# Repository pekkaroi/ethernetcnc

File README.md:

# ethernetcnc

This is my project for controlling CNC machine via ethernet port using LinuxCNC. It was originally shortly instroduced at http://pekka.eu/cnc. After receiving questions about it every now and then, I decided to publish it.

There is very little to no documentation about the project right now - hopefully that will change some day. There is the firmware for STM32F407, the kicad PCB and a LinuxCNC driver available.

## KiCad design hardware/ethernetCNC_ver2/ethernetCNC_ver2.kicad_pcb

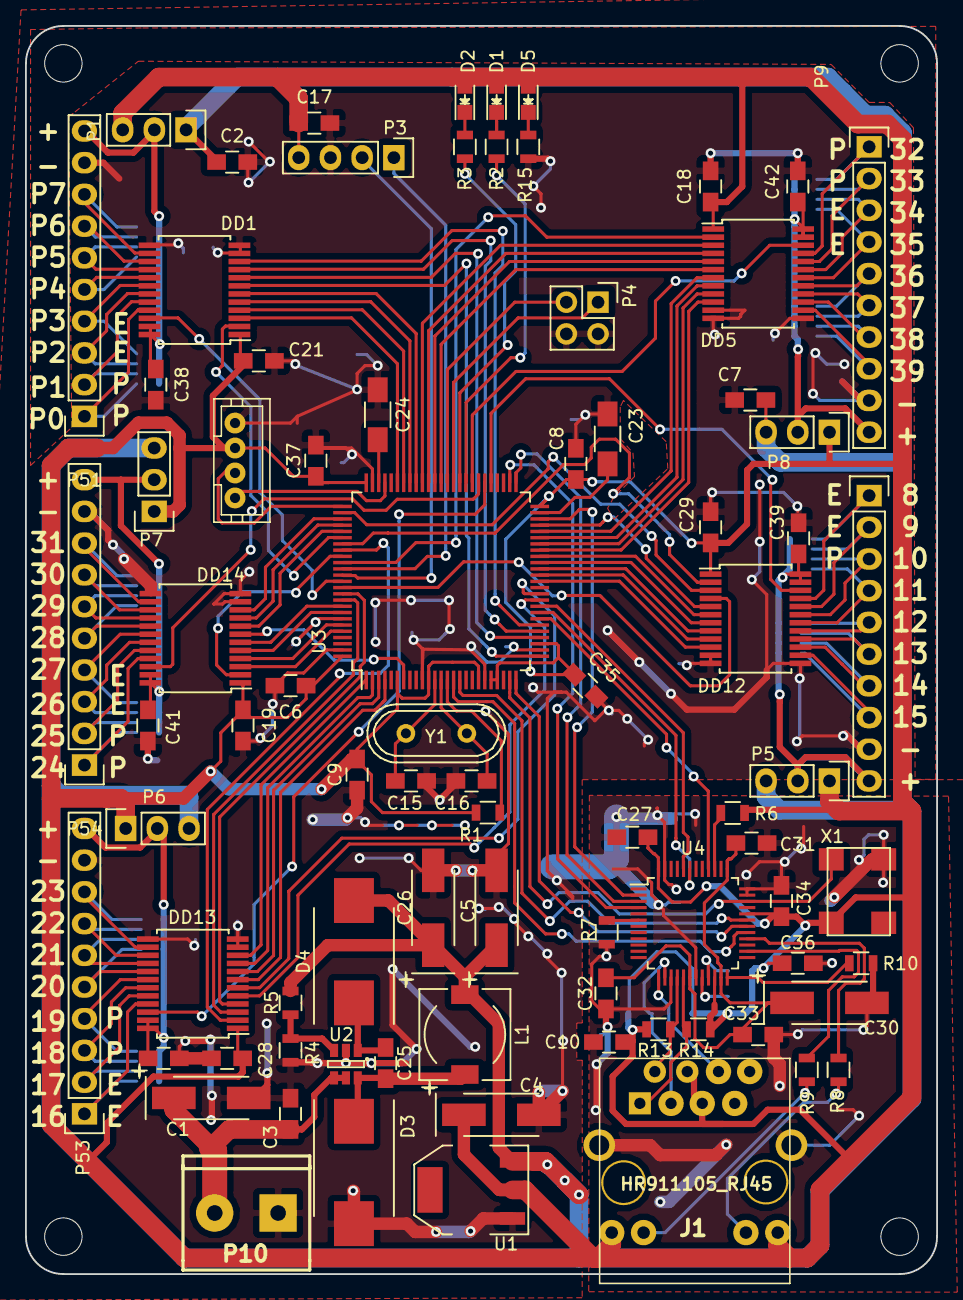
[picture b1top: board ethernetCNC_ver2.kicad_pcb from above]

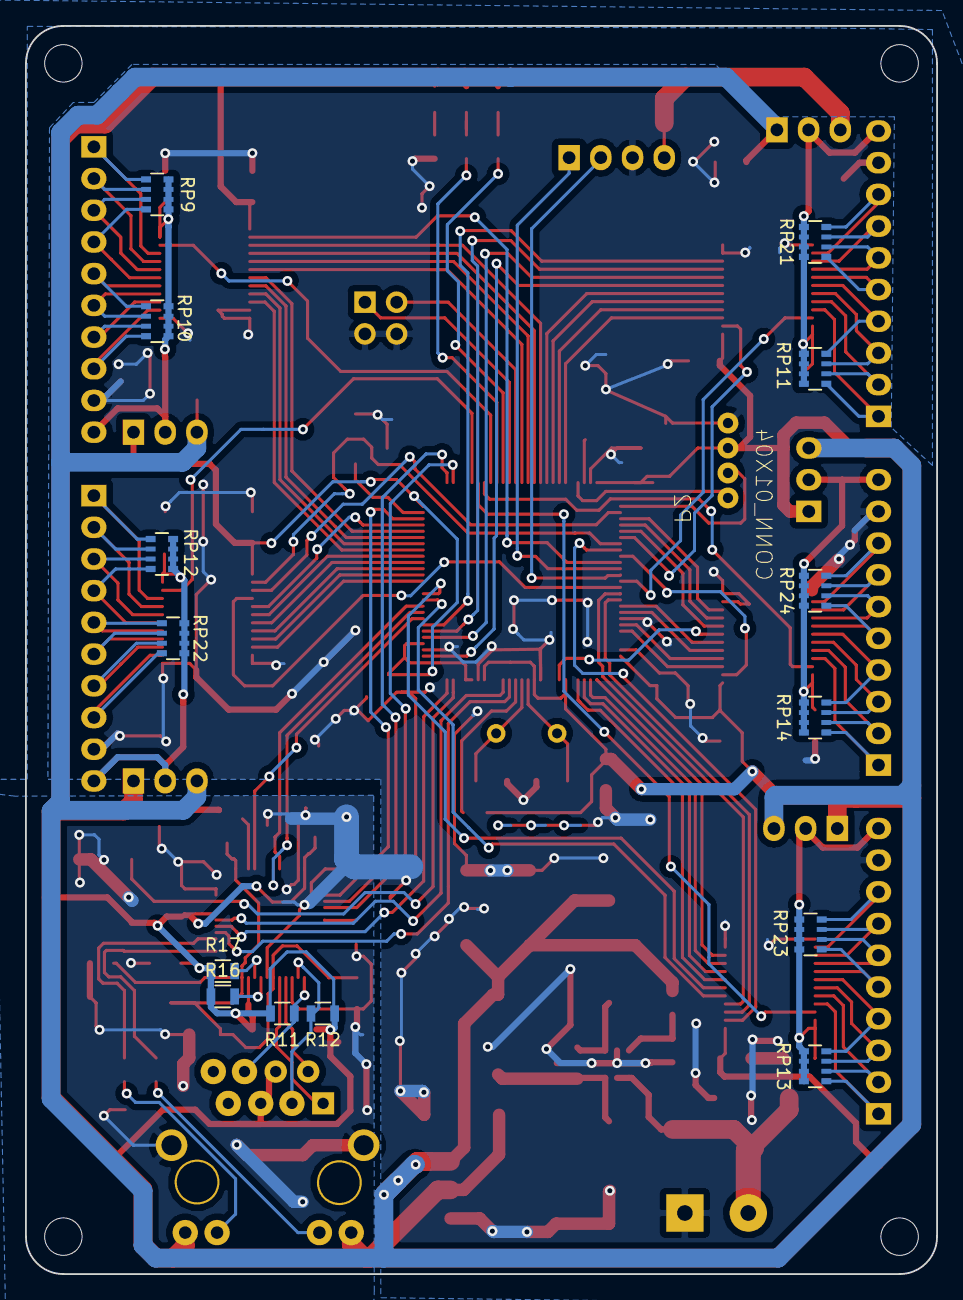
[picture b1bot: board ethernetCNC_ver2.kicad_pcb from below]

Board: 2 copper layers, 73.0 x 100.0 mm, 99 parts (14 on the bottom side), 142 nets.

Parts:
C1, C26: CP; TantalC_SizeC_EIA-6032_HandSoldering
C2, C3, C6, C7, C8, C9, C10, C17, C18, C19, C21, C25, C27, C28, C29, C31, C32, C33, C34, C35, C36, C37, C38, C39, C40, C41, C42: 100n; C_0805_HandSoldering
C4, C5, C30: 10u; TantalC_SizeC_EIA-6032_HandSoldering
C15, C16: 22p; C_0805_HandSoldering
C23, C24: 2.2u; C_1206_HandSoldering
D1, D2, D5: Led_Small; LED-0805
D3: D_Schottky_Small; DO-214AB_Handsoldering
D4: D; DO-214AB_Handsoldering
DD1, DD5, DD12, DD13, DD14: SN74LVC8T245; SSOP-24_5.3x8.2mm_Pitch0.65mm
J1: HR911105_RJ45
L1: L_Small; Choke_SMD_7.3x7.3_H3.5
P1, P5, P6, P7, P8: CONN_01X03; Pin_Header_Straight_1x03
P2: CONN_01X04; jst-ph-JST-PH4
P3: CONN_01X04; Pin_Header_Straight_1x04
P4: CONN_02X02; Pin_Header_Straight_2x02
P9, P51, P52, P53, P54: CONN_01X10; Pin_Header_Straight_1x10
P10: CONN_01X02; mors_2p
P11, P12, P13, P14: CONN_01X01; MountingHole_3mm
R1, R2, R3, R4, R5, R8, R9, R15, R16, R17: R; R_0805
R6, R7: 2k2; R_0805
R10: 4.87k 1%; R_0805
R11, R12, R13, R14: 50; R_0805
RP9, RP10, RP11, RP12, RP13, RP14, RP21, RP22, RP23, RP24: R_PACK4; R_Array_Convex_4x0603
U1: NCP1117ST50T3G; SOT-223
U2: LM2734; SOT-23-6
U3: STM32F407VG; LQFP-100_14x14mm_Pitch0.5mm
U4: DP83848; LQFP-48_7x7mm_Pitch0.5mm
X1: OSCILLATOR-VDD-4; OSC_4P_7050
Y1: Crystal_Small; Crystal_HC49-U_Vertical

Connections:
+3V3: C4.1, C6.1, C8.1, C9.1, C10.1, C17.1, C18.1, C19.1, C21.1, C27.1, C28.1, C29.1, C34.1, C35.1, C36.1, C37.1, D1.2, D2.2, D5.2, DD1.1, DD5.1, DD12.1, DD13.1, DD14.1, J1.4, J1.5, J1.9, J1.12, P1.3, P2.3, P3.4, P5.1, P6.1, P7.1, P8.1, R1.1, R6.2, R11.2, R12.1, R13.2, R14.1, R16.1, R17.1, U1.2, U3.6, U3.11, U3.19, U3.21, U3.22, U3.28, U3.50, U3.75, U3.100, U4.22, U4.32, U4.48, X1.4
+5V: C2.1, C5.1, C7.1, C26.1, D4.2, L1.2, P1.1, P5.3, P6.3, P7.3, P8.3, R5.1, U1.3
/Bank1/I1: DD1.3, U3.70
/Bank1/I2: DD1.4, U3.69
/Bank1/I5: DD1.7, U3.26
/Bank1/I6: DD1.8, U3.29
/Bank1/I7: DD1.9, U3.30
/Bank1/I8: DD1.10, U3.31
/Bank2/I3: DD12.5, U3.47
/Bank2/I4: DD12.6, U3.42
/Bank2/I5: DD12.7, U3.41
/Bank2/I6: DD12.8, U3.40
/Bank2/I7: DD12.9, U3.39
/Bank2/I8: DD12.10, U3.38
/Bank3/I3: DD13.5, U3.35
/Bank3/I4: DD13.6, U3.36
/Bank3/I5: DD13.7, U3.4
/Bank3/I6: DD13.8, U3.3
/Bank3/I7: DD13.9, U3.2
/Bank3/I8: DD13.10, U3.1
/Bank4/I1: DD14.3, U3.96
/Bank4/I2: DD14.4, U3.95
/Bank4/I5: DD14.7, U3.7
/Bank4/I6: DD14.8, U3.80
/Bank4/I7: DD14.9, U3.79
/Bank4/I8: DD14.10, U3.78
/Bank5/I1: DD5.3, U3.66
/Bank5/I2: DD5.4, U3.65
/Bank5/I5: DD5.7, U3.46
/Bank5/I6: DD5.8, U3.45
/Bank5/I7: DD5.9, U3.44
/Bank5/I8: DD5.10, U3.43
/VIN: C1.1, C3.1, P10.2, U2.4, U2.5
/uC/BANK1_DIR: DD1.2, U3.81
/uC/BANK1_OE: DD1.22, U3.88
/uC/BANK2_DIR: DD12.2, U3.82
/uC/BANK2_OE: DD12.22, U3.55
/uC/BANK3_DIR: DD13.2, U3.83
/uC/BANK3_OE: DD13.22, U3.56
/uC/BANK4_DIR: DD14.2, U3.84
/uC/BANK4_OE: DD14.22, U3.57
/uC/BANK5_DIR: DD5.2, U3.85
/uC/BANK5_OE: DD5.22, U3.58
/uC/CRS: U3.32, U4.40
/uC/ELED0: J1.10, R9.1
/uC/ELED1: J1.11, R8.1
/uC/ENC1A: DD1.6, U3.67
/uC/ENC1B: DD1.5, U3.68
/uC/ENC2A: DD12.3, U3.77
/uC/ENC2B: DD12.4, U3.89
/uC/ENC3A: DD13.4, U3.90
/uC/ENC3B: DD13.3, U3.91
/uC/ENC4A: DD14.6, U3.92
/uC/ENC4B: DD14.5, U3.93
/uC/ENC8A: DD5.6, U3.63
/uC/ENC8B: DD5.5, U3.64
/uC/EOSC: U3.24, U4.34, X1.3
/uC/ERESET: U3.15, U4.29
/uC/LED0: R2.2, U3.59
/uC/LED1: R3.2, U3.60
/uC/MDC: U3.16, U4.31
/uC/MDIO: U3.25, U4.30
/uC/RX0: U3.33, U4.43
/uC/RX1: U3.34, U4.44
/uC/STATUS0: P4.1, U3.61
/uC/STATUS1: P4.3, U3.62
/uC/TX0: U3.51, U4.3
/uC/TX1: U3.52, U4.4
/uC/TX_EN: U3.48, U4.2
GND: C1.2, C2.2, C3.2, C4.2, C5.2, C6.2, C7.2, C8.2, C9.2, C10.2, C15.2, C16.2, C17.2, C18.2, C19.2, C21.2, C23.2, C24.2, C26.2, C27.2, C28.2, C29.2, C30.2, C31.2, C32.2, C33.2, C34.2, C35.2, C36.2, C37.2, C38.2, C39.2, C40.2, C41.2, C42.2, D3.2, DD1.11, DD1.12, DD1.13, DD5.11, DD5.12, DD5.13, DD12.11, DD12.12, DD12.13, DD13.11, DD13.12, DD13.13, DD14.11, DD14.12, DD14.13, J1.0, P2.4, P3.3, P4.2, P4.4, P9.9, P10.1, P51.9, P52.9, P53.9, P54.9, R4.1, R7.1, R10.1, R15.2, U1.1, U2.2, U3.10, U3.20, U3.27, U3.74, U3.94, U3.99, U4.15, U4.19, U4.35, U4.36, U4.47, X1.2
unnamed: C15.1, U3.12, Y1.1
unnamed: C16.1, U3.13, Y1.2
unnamed: C23.1, U3.49
unnamed: C24.1, U3.73
unnamed: C25.1, D4.1, U2.1
unnamed: C25.2, D3.1, L1.1, U2.6
unnamed: C30.1, C31.1, C32.1, C33.1, U4.18, U4.23, U4.37
unnamed: C38.1, DD1.23, DD1.24, P1.2, P51.10, RP11.1, RP11.2, RP11.3, RP11.4, RP21.1, RP21.2, RP21.3, RP21.4
unnamed: C39.1, DD12.23, DD12.24, P5.2, P52.10, RP12.1, RP12.2, RP12.3, RP12.4, RP22.1, RP22.2, RP22.3, RP22.4
unnamed: C40.1, DD13.23, DD13.24, P6.2, P53.10, RP13.1, RP13.2, RP13.3, RP13.4, RP23.1, RP23.2, RP23.3, RP23.4
unnamed: C41.1, DD14.23, DD14.24, P7.2, P54.10, RP14.1, RP14.2, RP14.3, RP14.4, RP24.1, RP24.2, RP24.3, RP24.4
unnamed: C42.1, DD5.23, DD5.24, P8.2, P9.10, RP9.1, RP9.2, RP9.3, RP9.4, RP10.1, RP10.2, RP10.3, RP10.4
unnamed: D1.1, R2.1
unnamed: D2.1, R3.1
unnamed: D5.1, R15.1
unnamed: DD1.14, P51.8, RP21.8
unnamed: DD1.15, P51.7, RP21.7
unnamed: DD1.16, P51.6, RP21.6
unnamed: DD1.17, P51.5, RP21.5
unnamed: DD1.18, P51.4, RP11.8
unnamed: DD1.19, P51.3, RP11.7
unnamed: DD1.20, P51.2, RP11.6
unnamed: DD1.21, P51.1, RP11.5
unnamed: DD5.14, P9.8, RP10.8
unnamed: DD5.15, P9.7, RP10.7
unnamed: DD5.16, P9.6, RP10.6
unnamed: DD5.17, P9.5, RP10.5
unnamed: DD5.18, P9.4, RP9.8
unnamed: DD5.19, P9.3, RP9.7
unnamed: DD5.20, P9.2, RP9.6
unnamed: DD5.21, P9.1, RP9.5
unnamed: DD12.14, P52.8, RP22.8
unnamed: DD12.15, P52.7, RP22.7
unnamed: DD12.16, P52.6, RP22.6
unnamed: DD12.17, P52.5, RP22.5
unnamed: DD12.18, P52.4, RP12.8
unnamed: DD12.19, P52.3, RP12.7
unnamed: DD12.20, P52.2, RP12.6
unnamed: DD12.21, P52.1, RP12.5
unnamed: DD13.14, P53.8, RP23.8
unnamed: DD13.15, P53.7, RP23.7
unnamed: DD13.16, P53.6, RP23.6
unnamed: DD13.17, P53.5, RP23.5
unnamed: DD13.18, P53.4, RP13.8
unnamed: DD13.19, P53.3, RP13.7
unnamed: DD13.20, P53.2, RP13.6
unnamed: DD13.21, P53.1, RP13.5
unnamed: DD14.14, P54.8, RP24.8
unnamed: DD14.15, P54.7, RP24.7
unnamed: DD14.16, P54.6, RP24.6
unnamed: DD14.17, P54.5, RP24.5
unnamed: DD14.18, P54.4, RP14.8
unnamed: DD14.19, P54.3, RP14.7
unnamed: DD14.20, P54.2, RP14.6
unnamed: DD14.21, P54.1, RP14.5
unnamed: J1.1, R14.2, U4.17
unnamed: J1.2, R13.1, U4.16
unnamed: J1.3, R12.2, U4.14
unnamed: J1.6, R11.1, U4.13
unnamed: P2.1, U3.72
unnamed: P2.2, U3.76
unnamed: P3.1, U3.86
unnamed: P3.2, U3.87
unnamed: R1.2, U3.14
unnamed: R4.2, R5.2, U2.3
unnamed: R6.1, U4.39
unnamed: R7.2, U4.6
unnamed: R8.2, U4.28
unnamed: R9.2, U4.26
unnamed: R10.2, U4.24
unnamed: R16.2, U4.20
unnamed: R17.2, U4.21

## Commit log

2018-10-19 Update ethernet_rt.c
    typo
